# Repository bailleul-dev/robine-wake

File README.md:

# Robine Wake

Robine Wake is a privacy-first smart alarm clock for Raspberry Pi 3, Nerves,
and HiFiBerry, with a planned DIY bed-vibration channel for breathing, music
and progressive waking. The MVP runs fully on `host` with simulated
hardware, while preserving target adapters for the real device.

The product scope was updated on 2026-09-06: camera and bed-presence features are
removed. Their existing implementation still needs removal; the tactile extension
is specified but not implemented. See the
[bed-vibration specification](docs/specs/30/004-bed-vibration/spec.md) and the
[scope and migration status](docs/MVP_STATUS.md).

## Run on a development computer

Copy the public environment template once. The resulting `.env` is ignored by
Git and is loaded automatically by the Make targets and release scripts:

```sh
cp .env.dist .env
```

The host build does not require any private value. Leave optional entries empty
when they do not apply to your setup.

If a credential was committed before this setup existed, moving it to `.env`
does not remove it from Git history. Rotate that credential and either publish
from a fresh history or purge the old objects before making the repository
public.

```sh
mix deps.get
mix verify
mix run --no-halt
```

`mix verify` checks formatting, compiles with warnings treated as errors, runs
Credo in strict mode, audits Hex dependencies, and runs the complete host suite.
ExCoveralls enforces 67% production-code coverage and writes the browsable report
to `cover/excoveralls.html`; test-support modules are excluded from the metric.
The command also writes the scenario and requirements summary to
`cover/mvp-report.json`.

The individual quality checks are available while iterating:

```sh
mix credo --strict
mix coveralls
mix coveralls.html
```

Open <http://localhost:4110>. The local web interface has no login or password.
The HTTP port can be changed with `ROBINE_WEB_PORT`.

An MCP Streamable HTTP endpoint is available at
`http://localhost:4110/mcp`. It exposes device state and revision-safe alarm and
wake-session tools. Configure the client on the trusted local network and see
the [HTTP MCP specification](docs/specs/50/002-http-mcp/spec.md) for the complete
contract and security profile.

The host build also starts a Phoenix LiveView Hardware Lab at
<http://127.0.0.1:4111>. It emulates HiFiBerry availability and failures, network
loss, clock trust,
deterministic time advancement, alarms, snooze, and dismissal through the real
domain processes. Existing camera simulation controls are legacy functionality
scheduled for removal; tactile simulation is specified and remains to be added.
Change its port with `ROBINE_DEV_PORT`. The laboratory is loopback-only and its
Phoenix/LiveView code is excluded from Raspberry Pi compilation. See the
[host hardware emulator specification](docs/specs/80/002-host-hardware-emulator/spec.md).

### Demo mode

The same server can run as a public demo on a standard server, with the
hardware emulated: the product web app and a photoreal 3D bedroom (the sound
bar, its lights, the bedside remote, the sound) side by side at `/demo`. Every
action goes through the real server logic, routed to emulated drivers, with an
accelerated clock to watch a dawn in a few minutes.

```sh
ROBINE_DEMO=1 ROBINE_DEMO_ACCESS_CODE=change-me mix run --no-halt
open http://localhost:8080/demo
```

With Docker (set `ROBINE_DEMO_ACCESS_CODE` in `.env`):

```sh
docker compose up -d --build
```

The image uses the committed web build in `priv/web`; run `make expo-web`
first to refresh it. See the
[demo deployment section](docs/specs/80/002-host-hardware-emulator/spec.md#demo-deployment).

The public instance runs in the k3s cluster managed by `../silo01`, like the
other apps there. `make docker-build-and-push` builds the image for the
cluster, tagged with the current commit (uncommitted changes are refused), and
pushes it to the registry; `make robine-wake-demo-deploy ROBINE_WAKE_DEMO_VERSION=<tag>`
in `../silo01` rolls it out to <https://robine-wake-demo.bailleul.dev/demo>.
A demo release is a `demo-v*` tag of main (`make demo-release RELEASE=demo-v0.2.0`):
its CI (`.github/workflows/ci.yml`, on robine-actions' runners) runs the host
tests, builds and pushes the image tagged with it, then robine-actions rolls it
out; silo01 never builds.

The Raspberry Pi web interface is intentionally passwordless and intended only
for the trusted local network. Firmware updates and SSH remain authenticated.

## Experimental prototypes

The [`experimental/`](experimental/README.md) directory holds throwaway
evaluation prototypes that are **not part of the product**: they are not built
by `mix verify`, not shipped in the firmware, not deployed in the demo. The
current one is a Rust port of the alarm API used to evaluate a future
Buildroot-based system on custom hardware.

## Website and documentation

The marketing page and the technical documentation (generated from `docs/`) live
in [`website/`](website/README.md), an Astro / Starlight project:
`make site-dev`, `make site-build`.

## Mobile app

The iOS and Android application is the Expo / React Native project, written in
Gleam, in
[`mobile/`](mobile/README.md). `make expo-iphone` installs it on a local iPhone,
`make ios-beta` uploads it to TestFlight and `make play-store` to Google Play.

> The BLE control service is disabled on the Raspberry Pi firmware: the onboard
> controller now serves the [Bluetooth audio receiver](docs/specs/30/005-bluetooth-audio-receiver/spec.md).
> On the device, the app only reaches the clock over Wi-Fi.

The stable versioned command envelope, GATT UUIDs, paged response header, CRC32
validation, compatibility rules, and supported operations are documented in the
[Bluetooth v1 contract](docs/bluetooth/v1.md).

## LED strip

The light comes from a 60-LED WS2812B strip driven by the ESP32 co-processor,
which the Pi commands over UART (`light.program`). No bridge, cloud account or
network light is involved.

- **Dawn.** Each alarm can raise a dawn on the strip over its pre-wake ramp, so
  that full daylight arrives at the alarm time. Snooze turns the strip off and
  resuming starts it again; dismissal turns it off or leaves it lit, per alarm.
- **Evening breathing.** The `Soir` screen starts a guided breathing session at
  a cadence picked from named patterns (or typed in) and a duration: the strip
  breathes while the speaker plays the meditation ambience at the chosen volume. An alarm takes over the strip.
- **Reading light.** On the `Soir` screen, a warm amber at the bottom of the
  vertical strip to read by, orange then red towards the top, for up to 4
  hours, then an optional sunset of up to 2 hours.
- **Ambience.** A program can play a sound along, such as the storm and rain:
  it lowers to silence as the light fades and stops with it.
- **Manual programs.** The same screen starts a sunrise or a sunset of 1 minute
  to 4 hours, or turns the strip off. It also reads the strip back, pixel by
  pixel.

Strip failures are logged and never prevent the local audio alarm from running.

## Build for Raspberry Pi 3

```sh
make firmware
```

Without Wi-Fi values in `.env`, the firmware still builds and uses Ethernet
only. Set `ROBINE_WIFI_SSID` and `ROBINE_WIFI_PASSPHRASE` to provision Wi-Fi in
your local image.

Production updates are accepted only when signed by the Ed25519 key whose
public half is embedded in the firmware. The private half is intentionally
kept outside the repository. Build and verify a signed update with:

```sh
scripts/build_signed_firmware.sh
```

For a headless first boot, provide the WPA2 network only while building. The
credentials are embedded in the resulting device image but are never written
to the repository or printed by the build:

```sh
cp .env.dist .env
# Fill ROBINE_WIFI_* and ROBINE_FWUP_PRIVATE_KEY in .env, then:
scripts/build_signed_firmware.sh
```

After flashing and booting, open `http://robine-wake.local:4000/`. Raspberry Pi
3 models without dual-band Wi-Fi must use a 2.4 GHz network.

On this development machine the generated private key is stored with mode
`0600` under `~/.config/robine-wake/`; back it up securely before relying on it
for deployed devices. Updates are refused while a wake session is active, when
the clock is untrusted, or within 15 minutes of the next alarm. Nerves then
uses its inactive A/B slot and startup validation guard.

The HiFiBerry Amp2 is validated as `plughw:0` with the
`hifiberry-dacplus` Device Tree overlay. Target firmware also advertises
`Robine Wake Bedroom` as an AirPlay 2 receiver (`robine-airplayd`). An alarm always preempts
an active stream and the receiver returns after alarm playback ends. Each alarm
selects two sounds: a progressive wake track and a strong fallback track that
starts if the gentle ramp completes without dismissal. Curated MP3 assets and
their manifest live in `priv/sounds`; validated custom WAV files remain under
the persistent `/data/sounds` directory. The DIY tactile assembly and its firmware
integration remain validation items. See
[the specifications](docs/specs/README.md) and
[the MVP implementation status](docs/MVP_STATUS.md). The
[requirements matrix](docs/REQUIREMENTS_TRACEABILITY.md) records verified,
partial, deferred, and hardware-dependent requirements individually.

### Arrêt du réveil

L’arrêt depuis l’iPhone et le web est désactivé côté réveil : le bouton physique
reste disponible. Le réglage distant est verrouillé, y compris lorsqu’une ancienne
préférence autorisait l’arrêt depuis le smartphone. La fonctionnalité est conservée
et peut être réactivée dans le firmware avec `remote_dismiss_enabled: true` dans
`config/config.exs`.

## Build for Raspberry Pi Zero W

The `rpi0` target (ARMv6, one core, 512 MB) reuses the application and the
Pi 3 build options, with its own system in `nerves_system_rpi0` (upstream Nerves
Zero system plus BlueZ/A2DP, `speaker-test` and the HiFiBerry overlays) and
its own `config/rpi0-config.txt` / `config/rpi0-fwup.conf`. The Pi 3 files are
unchanged.

```sh
make firmware-rpi0                      # MIX_TARGET=rpi0 make firmware
make burn-sd MIX_TARGET=rpi0 DEVICE=/dev/diskN
```

The Zero has no Ethernet: the micro-USB *data* port is an Ethernet gadget
(`usb0`) for a first access, and `wlan0` takes the Wi-Fi values from `.env`.
The LoRa radio is disabled on this target (its SPI chip select is claimed by the
amplifier HAT). The ESP32 guide light uses the same UART as the Pi 3 (GPIO 14/15):
the amplifier overlay is `merus-amp-uart` in `config/rpi0-config.txt`
(InnoMaker MA12070P HAT), the stock `merus-amp` overlay without its enable/mute
lines. See the wiring guide before connecting the ESP32. The first build
compiles the whole Buildroot system, which takes a while; it is not
cross-built from the Pi 3 artifacts.

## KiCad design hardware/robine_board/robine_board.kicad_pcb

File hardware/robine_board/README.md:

# Robine Wake — All-In-One Mainboard v1.1 (`robine_board`)

> **Statut : schéma v1.1 terminé, PCB placé mais non routé.** Les exports de
> fabrication (`exports/gerbers/`) reflètent cet état et **ne sont pas
> commandables**. La revue [`DESIGN_REVIEW.md`](DESIGN_REVIEW.md) porte sur la
> v1.0 ; une partie de ses points a été traitée par la v1.1.

Carte électronique principale tout-en-un du réveil / barre de son **Robine
Wake**, conçue sous **KiCad 9** via le serveur MCP `kicad`. Carte 2 couches,
120 × 90 mm, 145 composants.

Pour prototyper sans cette carte, voir le banc de dev sur breadboard :
[`../dev_bench/banc-de-dev.pdf`](../dev_bench/banc-de-dev.pdf).

---

## 1. Vue d'ensemble des sous-systèmes

| Sous-système | Référence(s) | Composant choisi | Caractéristiques clés |
| :--- | :--- | :--- | :--- |
| **MCU principal** | `U1`, `SW1`, `SW2`, `J3`, `U11`, `J4` | `ESP32-S3-WROOM-1-N16R8` | Dual-core LX7 240 MHz, 16 Mo flash, 8 Mo PSRAM octale, Wi-Fi + BLE 5. AirPlay 2, maître I²S, SPI et I²C. USB-C natif (`J3`, protection ESD `U11` `USBLC6-2SC6`, CC 5,1 kΩ `R22`/`R23`), console UART0 sur `J4` |
| **Co-processeur Bluetooth audio + aube** | `U2`, `J9`, `R25`, `R26`, `C29` | `ESP32-WROOM-32E` | Bluetooth Classic BR/EDR (A2DP sink, AVRCP), absent du S3. Esclave I²S de `U1` (`I2S_BCLK`, `I2S_LRCLK`), renvoie le flux A2DP sur `I2S_BT_DOUT`. Relié à `U1` par son UART0 ; `U1` pilote `BT_EN` et `BT_IO0` et peut le reflasher via le bootloader ROM. `J9` (`BT_PROG`) en parallèle pour la récupération manuelle. Génère aussi les 10 PWM de l'aube |
| **Entrée secteur 24 V** | `J1`, `D1`, `C1` | Bornier 2 points + `SS54` | Entrée `+24V_MAINS`, OR-ing vers `PVDD_24V` par `D1` |
| **UPS batterie 4S LiFePO4** | `J2`, `U3`, `Q1`, `L7`, `R15`, `R1`/`R2` | `BQ24610` + `CSD87350Q5D` | Chargeur buck synchrone depuis `+24V_MAINS`, shunt 10 mΩ, tension de fin de charge fixée par `R1`/`R2` (110 k / 20 k ≈ 13,6 V). `MAINS_OK` (/PG) et `CHG_STAT` (STAT1) vers `U1` |
| **Boost batterie → PVDD** | `U10`, `L8`, `D2`, `R16`/`R17`, `D3` | `TPS55340` | Remonte `+VBAT` vers ≈ 23,4 V sur `PVDD_24V` (OR-ing `D2`), activé par `BOOST_EN`. `D3` relie directement `+VBAT` à `PVDD_24V` en dernier recours |
| **Rails logiques** | `U4`, `L1`, `D5`, `U5`, `L6`, `D6` | `TPS54531` + `TPS54331` | Buck `PVDD_24V` → `+5V` (5 A, `R18`/`R19`), puis buck `+5V` → `+3V3` (3 A, `R20`/`R21`) |
| **Ampli stéréo** | `U6`, `L2..L5`, `C11..C14`, `C9`, `J5`, `R10` | `TAS5825M` (HTSSOP-32) | Classe D sur `PVDD_24V`, entrée I²S (`I2S_DOUT`), contrôle I²C, adresse fixée par `R10` (4,7 kΩ sur `ADR`). Filtre LC BTL vers `J5` (4 points) |
| **LoRa 868 MHz** | `U7`, `J6` | `Ai-Thinker Ra-01H` (SX1276) + SMA | Sur le SPI partagé, `LORA_CS`, `LORA_RST`, `LORA_DIO0`. Lien avec le bouton déporté `ACC-003` |
| **Stockage** | `U8` | `W25N01GVZEIG` | NAND SPI 1 Gbit sur le SPI partagé (`NAND_CS`) |
| **Horloge temps réel** | `U9`, `BT1` | `DS3231MZ` + CR1220 | I²C partagé avec l'ampli, alarme `RTC_INT_N` vers `U1`, sauvegarde par pile |
| **Lampes d'aube (10 canaux)** | `U12..U21`, `L11..L20`, `D11..D20`, `R31..R40`, `J7`, `J8`, `J10` | 10 × `PT4115` | Drivers LED à courant constant (shunt 0,2 Ω ≈ 0,5 A) alimentés par `+24V_MAINS`, gradation par `PWM_CH1..10` depuis `U2`. Lampe 1 (`J7`) et lampe 2 (`J8`) : blanc chaud, blanc froid, ambre. Halo (`J10`) : R, G, B, ambre |
| **LED de statut** | `D4`, `R9` | `SK6812` | Une LED adressable sur `+5V`, données `STATUS_LED_3V3` via 330 Ω |

---

## 2. Mapping GPIO de `U1` (`ESP32-S3-WROOM-1-N16R8`)

Généré à partir du netlist du schéma v1.1. Broches non listées : non connectées
(IO3, IO45, IO46 ; IO35..IO37 sont réservées à la PSRAM octale).

| Fonction | Net | Broche `U1` | GPIO | Cible(s) |
| :--- | :--- | :---: | :--- | :--- |
| Reset | `MCU_EN` | 3 | `EN` | `R24` 10 kΩ, `C7` 1 µF, bouton `SW1` |
| Boot | `MCU_BOOT` | 27 | `GPIO0` | `R12` 10 kΩ, bouton `SW2` |
| Présence secteur | `MAINS_OK` | 4 | `GPIO4` | `U3` /PG, pull-up `R8` |
| Commande boost | `BOOST_EN` | 5 | `GPIO5` | `U10` EN, pull-down `R13` |
| ADC batterie | `ADC_VBAT_SENSE` | 39 | `GPIO1` (ADC1_CH0) | Pont `R3` 100 kΩ / `R4` 15 kΩ sur `+VBAT` |
| État charge | `CHG_STAT` | 38 | `GPIO2` | `U3` STAT1, pull-up `R5` |
| I²S horloge bit | `I2S_BCLK` | 6 | `GPIO6` | `U6` SCLK + `U2` IO26 |
| I²S horloge mot | `I2S_LRCLK` | 7 | `GPIO7` | `U6` LRCLK + `U2` IO25 |
| I²S vers ampli | `I2S_DOUT` | 12 | `GPIO8` | `U6` SDIN |
| I²S depuis BT | `I2S_BT_DOUT` | 33 | `GPIO40` | `U2` IO22 (flux A2DP) |
| I²C données | `I2C_SDA` | 10 | `GPIO17` | `U6`, `U9`, pull-up `R6` 4,7 kΩ |
| I²C horloge | `I2C_SCL` | 11 | `GPIO18` | `U6`, `U9`, pull-up `R7` 4,7 kΩ |
| Ampli marche | `AMP_PDN` | 23 | `GPIO21` | `U6` /PDN |
| Ampli défaut | `AMP_FAULT` | 31 | `GPIO38` | `U6` /FAULT, pull-up `R11` |
| SPI horloge | `SPI_SCK` | 20 | `GPIO12` | `U7`, `U8` |
| SPI MOSI | `SPI_MOSI` | 19 | `GPIO11` | `U7`, `U8` |
| SPI MISO | `SPI_MISO` | 21 | `GPIO13` | `U7`, `U8` |
| LoRa sélection | `LORA_CS` | 18 | `GPIO10` | `U7` NSS, pull-up `R27` |
| LoRa reset | `LORA_RST` | 22 | `GPIO14` | `U7` RESET |
| LoRa interruption | `LORA_DIO0` | 32 | `GPIO39` | `U7` DIO0 |
| NAND sélection | `NAND_CS` | 17 | `GPIO9` | `U8` /CS, pull-up `R28` |
| RTC alarme | `RTC_INT_N` | 34 | `GPIO41` | `U9` /INT, pull-up `R14` |
| LED statut | `STATUS_LED_3V3` | 35 | `GPIO42` | `R9` 330 Ω → `D4` DIN |
| Liaison BT (TX de `U1`) | `BT_RXD0` | 8 | `GPIO15` | `U2` RXD0, `J9` broche 3 |
| Liaison BT (RX de `U1`) | `BT_TXD0` | 9 | `GPIO16` | `U2` TXD0, `J9` broche 2 |
| Reset de `U2` | `BT_EN` | 24 | `GPIO47` | `U2` EN, `R25`, `C29`, `J9` broche 5 — en open-drain |
| Boot de `U2` | `BT_IO0` | 25 | `GPIO48` | `U2` IO0, `R26`, `J9` broche 4 — en open-drain |
| USB natif | `USB_DN`, `USB_DP` | 13, 14 | `GPIO19`, `GPIO20` | `U11` → `J3` |
| Console | `UART0_TX`, `UART0_RX` | 37, 36 | `GPIO43`, `GPIO44` | `J4` |

Quand un adaptateur est branché sur `J9`, laisser `GPIO15` en entrée : il est
en parallèle de la sortie TX de l'adaptateur.

## 3. Mapping GPIO de `U2` (`ESP32-WROOM-32E`)

| Fonction | Net | GPIO | Cible |
| :--- | :--- | :--- | :--- |
| Liaison avec `U1` | `BT_RXD0`, `BT_TXD0` | `GPIO3`, `GPIO1` (UART0) | `U1` GPIO15, GPIO16 |
| Reset, boot | `BT_EN`, `BT_IO0` | `EN`, `GPIO0` | `U1` GPIO47, GPIO48 |
| I²S esclave | `I2S_BCLK`, `I2S_LRCLK` | `GPIO26`, `GPIO25` | horloges générées par `U1` |
| Sortie A2DP | `I2S_BT_DOUT` | `GPIO22` | `U1` GPIO40 |
| Lampe 1 blanc chaud, froid, ambre | `PWM_CH1..3` | `GPIO4`, `GPIO13`, `GPIO14` | `U12..U14` DIM |
| Lampe 2 blanc chaud, froid, ambre | `PWM_CH4..6` | `GPIO18`, `GPIO19`, `GPIO21` | `U15..U17` DIM |
| Halo R, G, B, ambre | `PWM_CH7..10` | `GPIO23`, `GPIO27`, `GPIO32`, `GPIO33` | `U18..U21` DIM |

---

## 4. Vérifications

- **ERC** : 0 violation. **DRC** : 0 violation, parité schéma ↔ PCB sans
  écart ; 402 connexions restent à router.
- ERC et DRC ne contrôlent que la cohérence des symboles et empreintes tels
  que dessinés, pas leur conformité aux composants réels.

### Points ouverts

- **Routage** du PCB à faire, puis plans de masse et vias thermiques
  (`U6` PowerPAD, buck, boost).
- **Placement** : sur la vue 2D, des borniers et la zone d'antenne de `U1`
  débordent du contour de la carte.
- **Aube sur batterie** : les `PT4115` sont alimentés par `+24V_MAINS`, donc
  les lampes s'éteignent en cas de coupure secteur. À confirmer si c'est
  voulu.
- **LED de statut** : la `SK6812` est en 5 V et reçoit des données en 3,3 V
  sans level shifter ; le seuil haut (0,7 × VDD = 3,5 V) n'est pas garanti.

---

## 5. Fichiers

- **Sources KiCad**
  - [`robine_board.kicad_pro`](robine_board.kicad_pro) — projet KiCad 9
  - [`robine_board.kicad_sch`](robine_board.kicad_sch) — schéma
  - [`robine_board.kicad_pcb`](robine_board.kicad_pcb) — PCB 120 × 90 mm, placé, non routé
  - [`Robine_Custom.kicad_sym`](Robine_Custom.kicad_sym) — symboles dédiés
  - [`3dmodels/`](3dmodels) — modèles 3D des composants
- **Exports** (`exports/`, régénérés avec `kicad-cli` 9.0.8)
  - [`robine_board_schematic.pdf`](exports/robine_board_schematic.pdf), [`robine_board_schematic.png`](exports/robine_board_schematic.png) — schéma
  - [`robine_board_pcb.pdf`](exports/robine_board_pcb.pdf), [`robine_board_pcb.svg`](exports/robine_board_pcb.svg), [`robine_board_pcb_2d.png`](exports/robine_board_pcb_2d.png) — vue 2D (F.Cu, B.Cu, F.Silkscreen, Edge.Cuts)
  - [`robine_board_3d_iso.png`](exports/robine_board_3d_iso.png), [`robine_board_3d_top.png`](exports/robine_board_3d_top.png), [`robine_board_3d_bottom.png`](exports/robine_board_3d_bottom.png) — rendus 3D
  - [`robine_board.step`](exports/robine_board.step) — modèle 3D STEP
  - [`robine_board_bom.csv`](exports/robine_board_bom.csv) — nomenclature (145 composants, 68 lignes groupées)
  - [`robine_board_positions.csv`](exports/robine_board_positions.csv) — pick-and-place
  - [`drc_report.json`](exports/drc_report.json) — rapport DRC avec parité schéma
  - [`gerbers/`](exports/gerbers) — Gerber (cuivre, masque, pâte, sérigraphie, contour) et perçage Excellon, **non commandables tant que le PCB n'est pas routé**

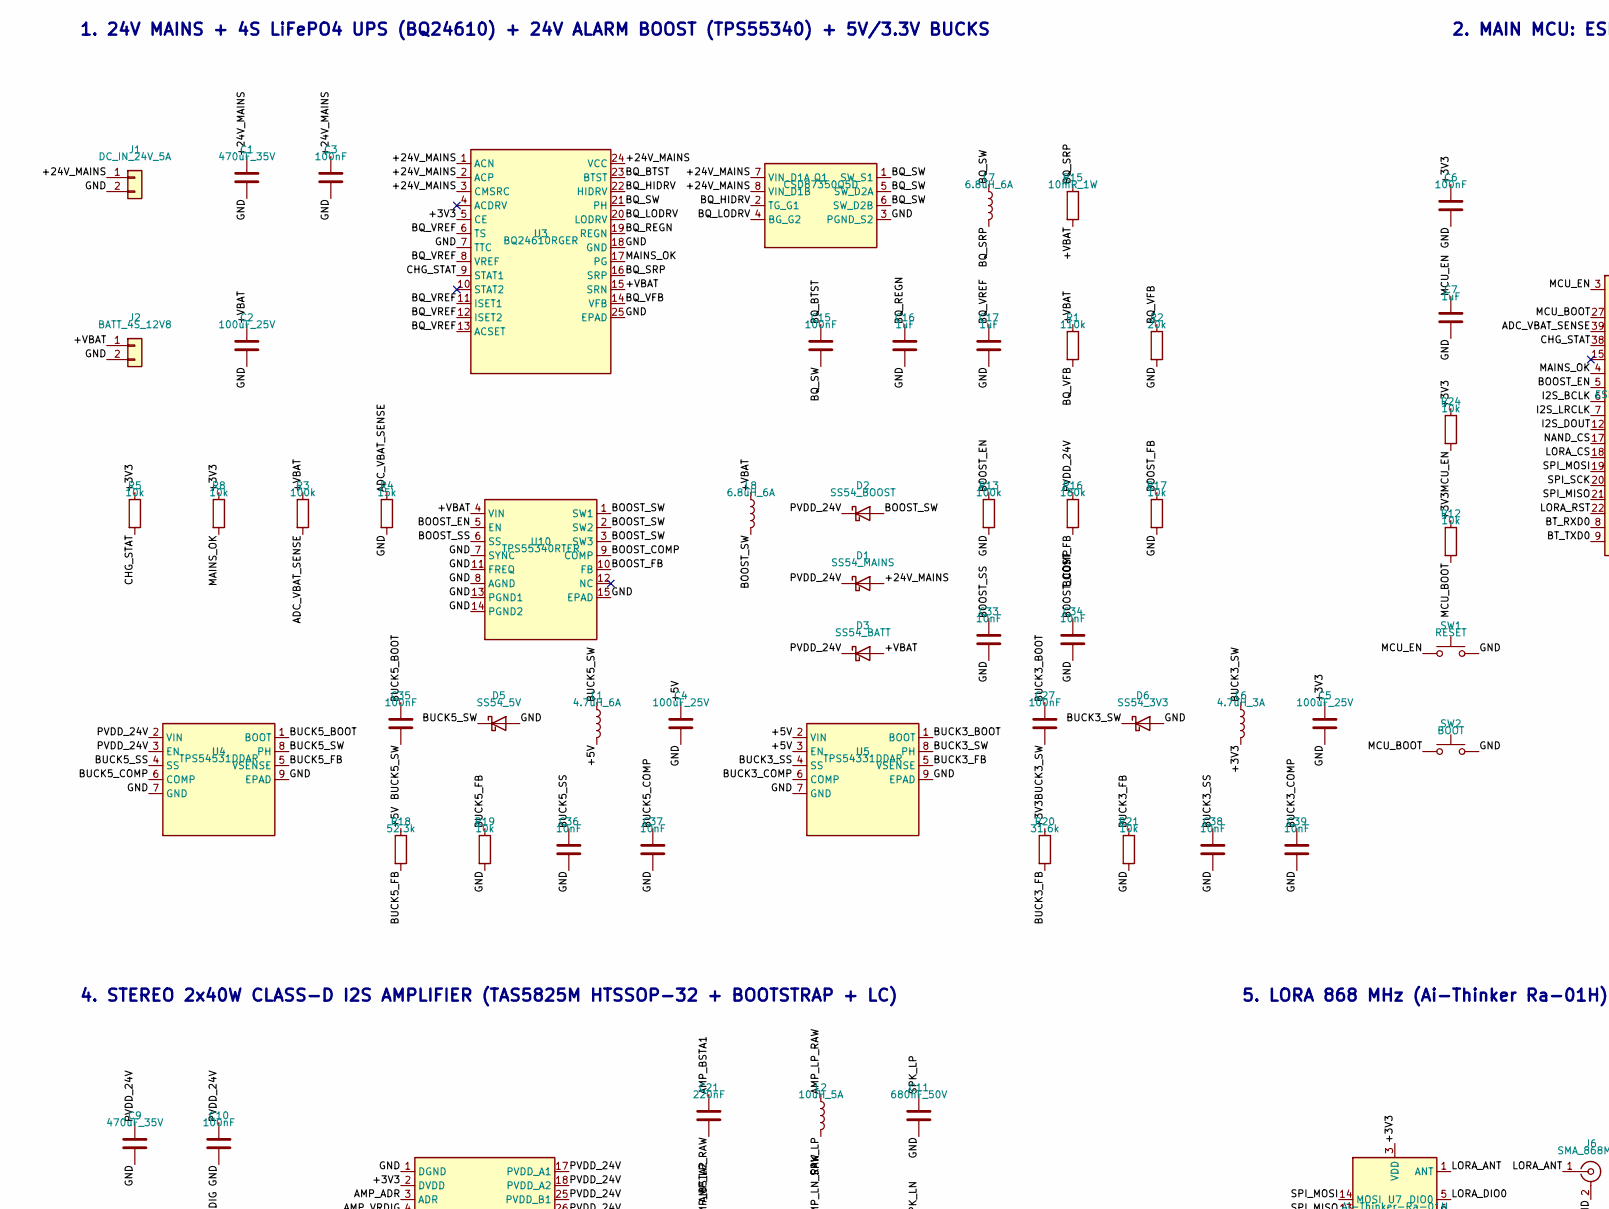
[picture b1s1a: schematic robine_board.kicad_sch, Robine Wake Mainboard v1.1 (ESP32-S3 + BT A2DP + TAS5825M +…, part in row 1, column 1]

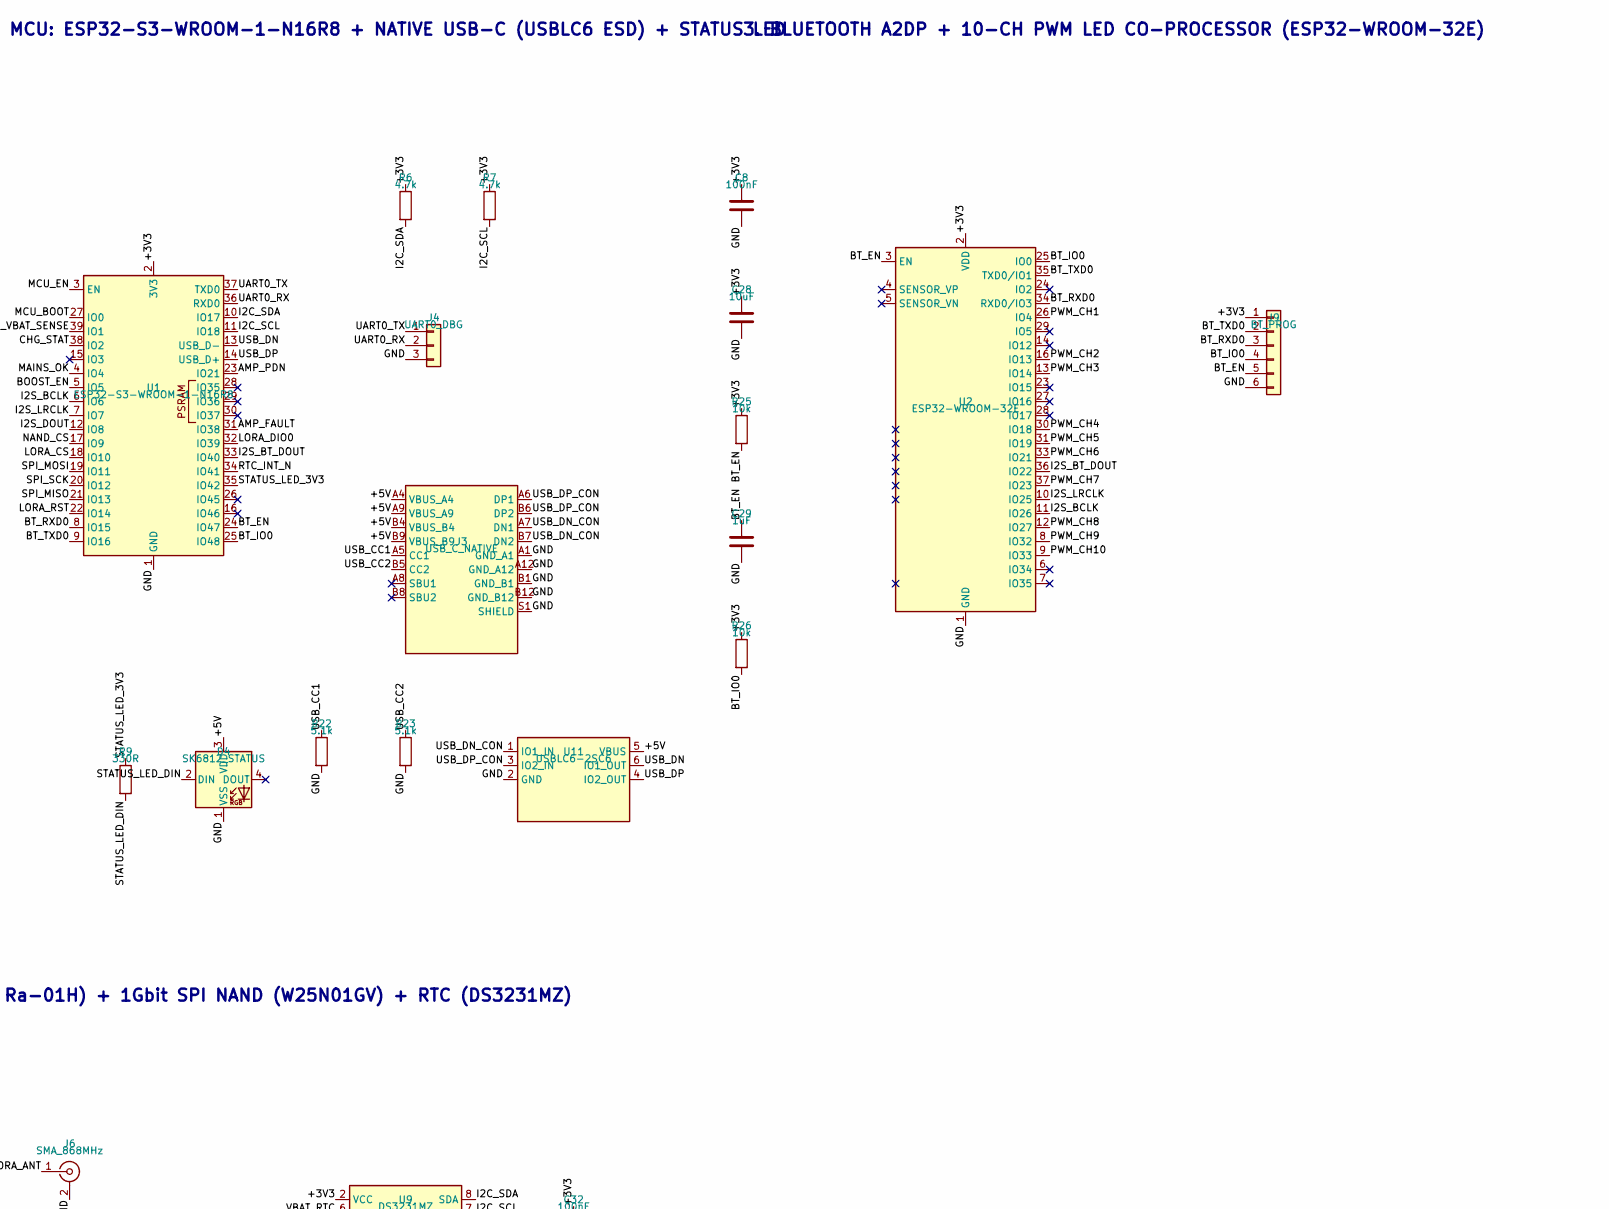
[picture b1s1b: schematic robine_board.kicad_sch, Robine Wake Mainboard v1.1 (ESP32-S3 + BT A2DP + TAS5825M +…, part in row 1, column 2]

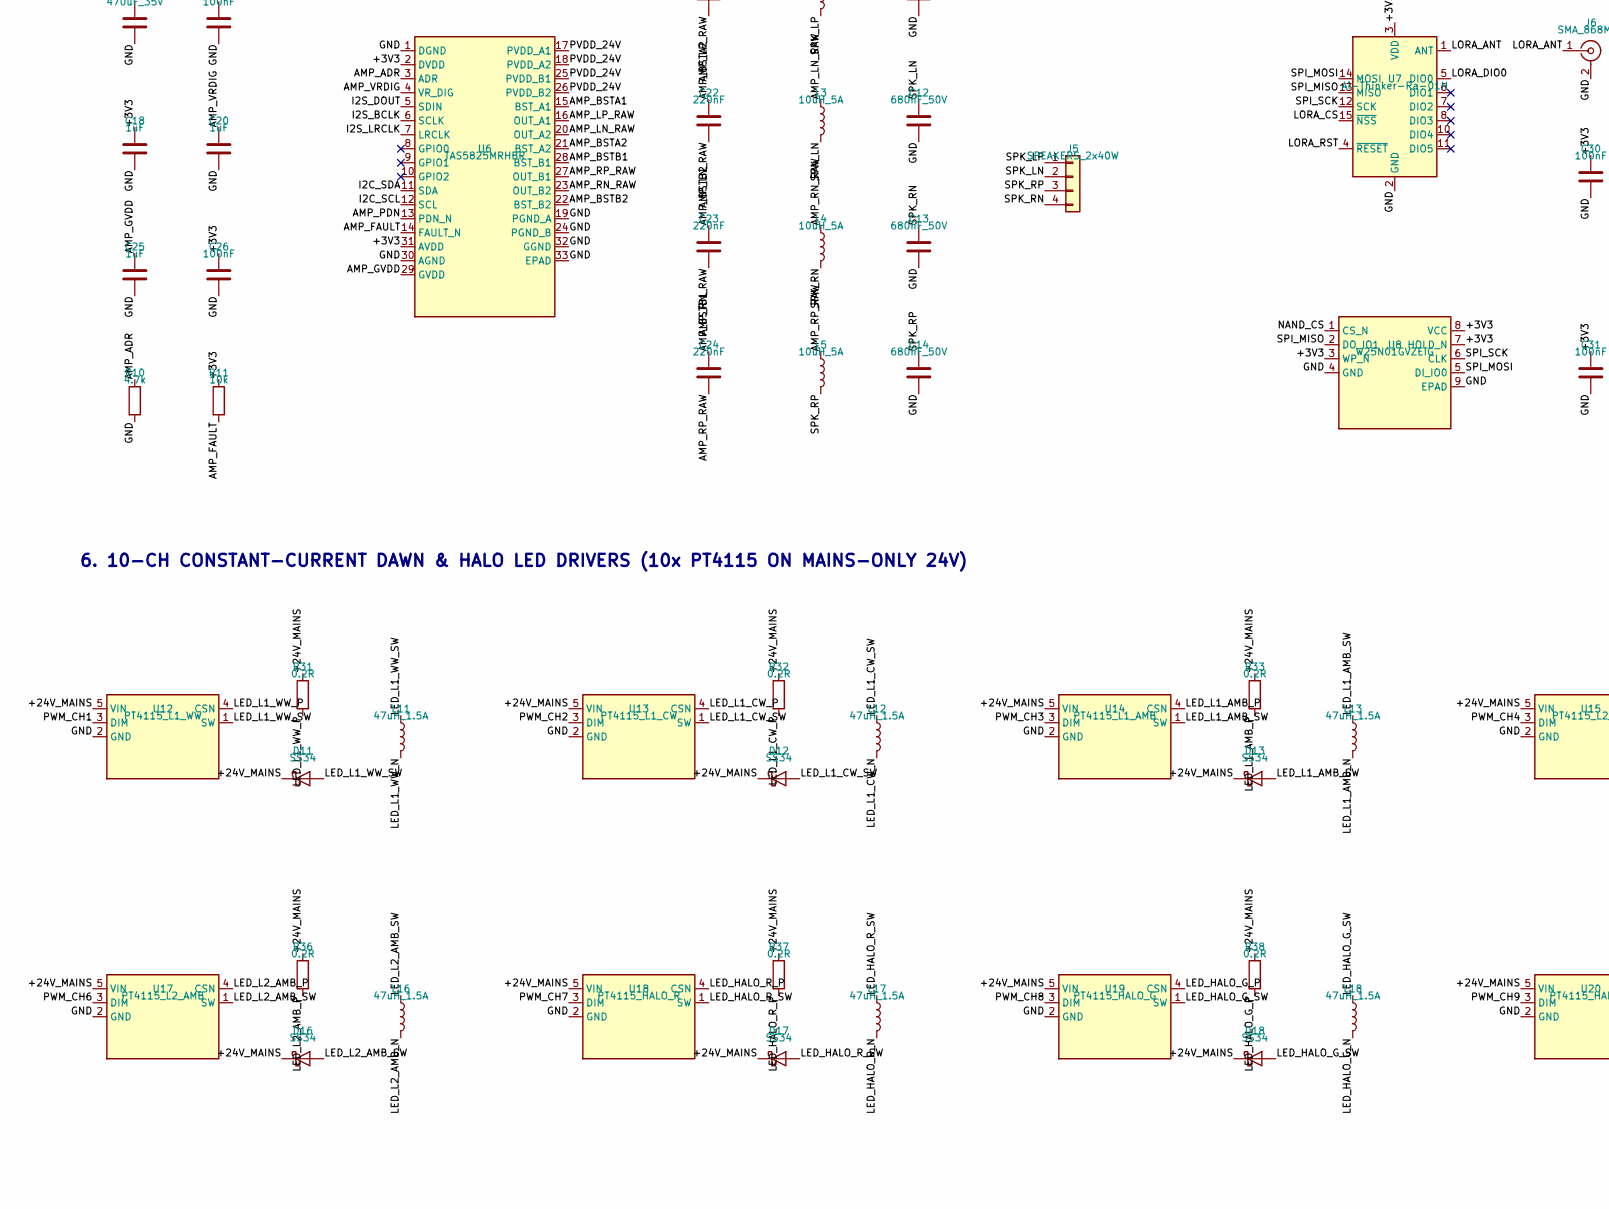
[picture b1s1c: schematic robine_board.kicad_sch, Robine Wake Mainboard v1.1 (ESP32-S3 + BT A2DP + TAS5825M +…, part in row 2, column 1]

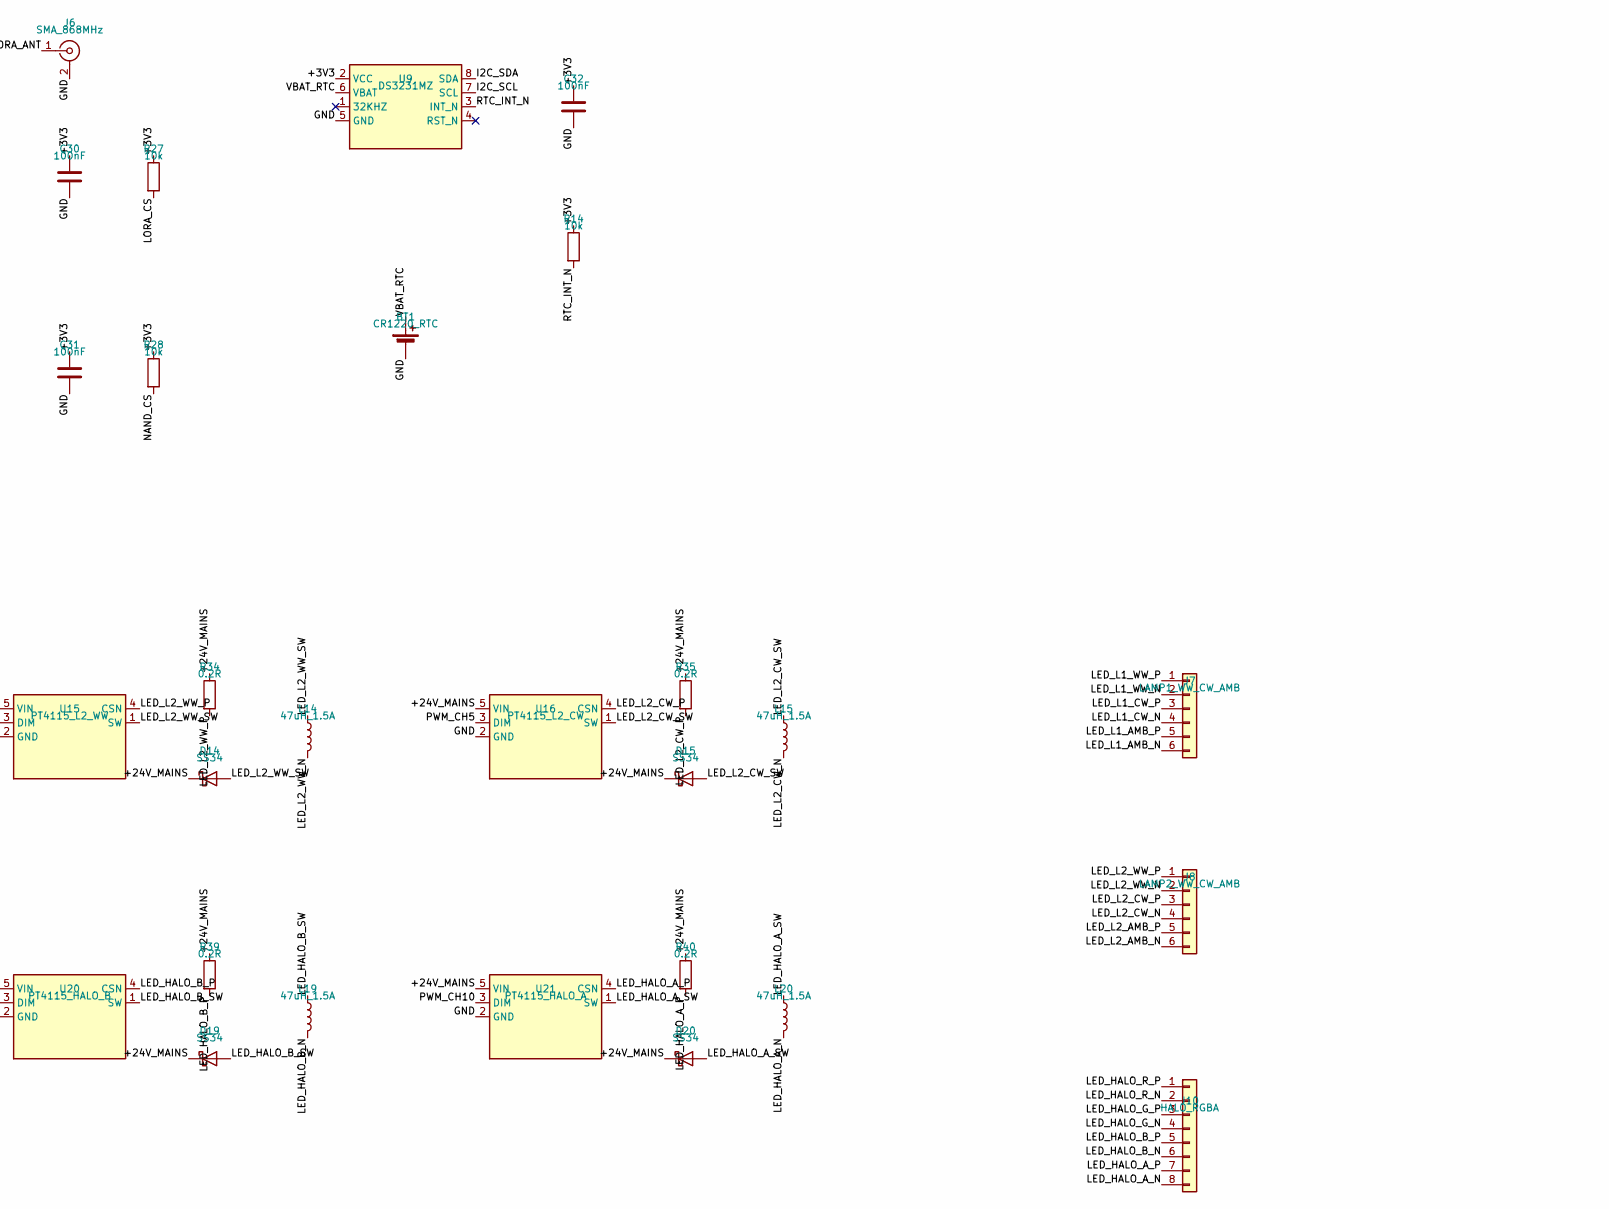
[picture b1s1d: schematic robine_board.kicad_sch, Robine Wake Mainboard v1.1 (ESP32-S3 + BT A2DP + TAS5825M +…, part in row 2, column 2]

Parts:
BT1: CR1220_RTC; Battery_Panasonic_CR1220-VCN_Vertical_CircularHoles
C1, C9: 470uF_35V; CP_Elec_10x10
C2, C4, C5: 100uF_25V; CP_Elec_6.3x7.7
C3, C6, C8, C10, C15, C26, C27, C30, C31, C32, C35: 100nF; C_0805_2012Metric
C7, C16, C17, C18, C20, C25, C29: 1uF; C_0805_2012Metric
C11, C12, C13, C14: 680nF_50V; C_0805_2012Metric
C21, C22, C23, C24: 220nF; C_0805_2012Metric
C28: 10uF; C_0805_2012Metric
C33, C34, C36, C37, C38, C39: 10nF; C_0805_2012Metric
D1: SS54_MAINS; D_SMA
D2: SS54_BOOST; D_SMA
D3: SS54_BATT; D_SMA
D4: SK6812_STATUS; LED_SK6812_PLCC4_5.0x5.0mm_P3.2mm
D5: SS54_5V; D_SMA
D6: SS54_3V3; D_SMA
D11, D12, D13, D14, D15, D16, D17, D18, D19, D20: SS34; D_SMA
J1: DC_IN_24V_5A; TerminalBlock_Phoenix_MKDS-1,5-2-5.08_1x02_P5.08mm_Horizont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
J2: BATT_4S_12V8; TerminalBlock_Phoenix_MKDS-1,5-2-5.08_1x02_P5.08mm_Horizont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
J3: USB_C_NATIVE; USB_C_Receptacle_GCT_USB4085
J4: UART0_DBG; PinHeader_1x03_P2.54mm_Vertical
J5: SPEAKERS_2x40W; TerminalBlock_Phoenix_MKDS-1,5-4-5.08_1x04_P5.08mm_Horizont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
J6: SMA_868MHz; SMA_Amphenol_132134_Vertical
J7: LAMP1_WW_CW_AMB; TerminalBlock_Phoenix_MKDS-1,5-6-5.08_1x06_P5.08mm_Horizont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
J8: LAMP2_WW_CW_AMB; TerminalBlock_Phoenix_MKDS-1,5-6-5.08_1x06_P5.08mm_Horizont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
J9: BT_PROG; PinHeader_1x06_P2.54mm_Vertical
J10: HALO_RGBA; TerminalBlock_Phoenix_MKDS-1,5-8-5.08_1x08_P5.08mm_Horizont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
L1: 4.7uH_6A; L_7.3x7.3_H4.5
L2, L3, L4, L5: 10uH_5A; L_7.3x7.3_H4.5
L6: 4.7uH_3A; L_6.3x6.3_H3
L7, L8: 6.8uH_6A; L_7.3x7.3_H4.5
L11, L12, L13, L14, L15, L16, L17, L18, L19, L20: 47uH_1.5A; L_6.3x6.3_H3
Q1: CSD87350Q5D; SOIC-8_3.9x4.9mm_P1.27mm
R1: 110k; R_0805_2012Metric
R2: 20k; R_0805_2012Metric
R3, R13: 100k; R_0805_2012Metric
R4: 15k; R_0805_2012Metric
R5, R8, R11, R12, R14, R17, R19, R21, R24, R25, R26, R27, R28: 10k; R_0805_2012Metric
R6, R7, R10: 4.7k; R_0805_2012Metric
R9: 330R; R_0805_2012Metric
R15: 10mR_1W; R_1206_3216Metric
R16: 180k; R_0805_2012Metric
R18: 52.3k; R_0805_2012Metric
R20: 31.6k; R_0805_2012Metric
R22, R23: 5.1k; R_0805_2012Metric
R31, R32, R33, R34, R35, R36, R37, R38, R39, R40: 0.2R; R_0805_2012Metric
SW1: RESET; SW_SPST_PTS645Sx43SMTR92
SW2: BOOT; SW_SPST_PTS645Sx43SMTR92
U1: ESP32-S3-WROOM-1-N16R8; ESP32-S3-WROOM-1
U2: ESP32-WROOM-32E
U3: BQ24610RGER; HVQFN-24-1EP_4x4mm_P0.5mm_EP2.5x2.5mm
U4: TPS54531DDAR; SOIC-8-1EP_3.9x4.9mm_P1.27mm_EP2.29x3mm
U5: TPS54331DDAR; SOIC-8-1EP_3.9x4.9mm_P1.27mm_EP2.29x3mm
U6: TAS5825MRHBR; HTSSOP-32-1EP_6.1x11mm_P0.65mm_EP5.2x11mm_Mask4.11x4.36mm
U7: Ai-Thinker-Ra-01H; Ai-Thinker-Ra-01-LoRa
U8: W25N01GVZEIG; WSON-8-1EP_8x6mm_P1.27mm_EP3.4x4.3mm
U9: DS3231MZ; SOIC-8_3.9x4.9mm_P1.27mm
U10: TPS55340RTER; Texas_HTSSOP-14-1EP_4.4x5mm_P0.65mm_EP3.4x5mm_Mask3.155x3.2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
U11: USBLC6-2SC6; SOT-23-6
U12: PT4115_L1_WW; SOT-89-5
U13: PT4115_L1_CW; SOT-89-5
U14: PT4115_L1_AMB; SOT-89-5
U15: PT4115_L2_WW; SOT-89-5
U16: PT4115_L2_CW; SOT-89-5
U17: PT4115_L2_AMB; SOT-89-5
U18: PT4115_HALO_R; SOT-89-5
U19: PT4115_HALO_G; SOT-89-5
U20: PT4115_HALO_B; SOT-89-5
U21: PT4115_HALO_A; SOT-89-5

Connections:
/+3V3: C5.1, C6.1, C8.1, C18.1, C26.1, C28.1, C30.1, C31.1, C32.1, J9.1, L6.2, R5.1, R6.1, R7.1, R8.1, R11.1, R12.1, R14.1, R20.1, R24.1, R25.1, R26.1, R27.1, R28.1, U1.2 (3V3), U2.2 (VDD), U3.5 (CE), U6.2 (DVDD), U6.31 (AVDD), U7.3 (VDD), U8.3 (WP_N), U8.7 (HOLD_N), U8.8 (VCC), U9.2 (VCC)
/+5V: C4.1, D4.3 (VDD), J3.A4 (VBUS_A4), J3.A9 (VBUS_A9), J3.B4 (VBUS_B4), J3.B9 (VBUS_B9), L1.2, R18.1, U5.2 (VIN), U5.3 (EN), U11.5 (VBUS)
/+24V_MAINS: C1.1, C3.1, D1.2 (A), D11.1 (K), D12.1 (K), D13.1 (K), D14.1 (K), D15.1 (K), D16.1 (K), D17.1 (K), D18.1 (K), D19.1 (K), D20.1 (K), J1.1, Q1.7 (VIN_D1A), Q1.8 (VIN_D1B), R31.1, R32.1, R33.1, R34.1, R35.1, R36.1, R37.1, R38.1, R39.1, R40.1, U3.1 (ACN), U3.2 (ACP), U3.3 (CMSRC), U3.24 (VCC), U12.5 (VIN), U13.5 (VIN), U14.5 (VIN), U15.5 (VIN), U16.5 (VIN), U17.5 (VIN), U18.5 (VIN), U19.5 (VIN), U20.5 (VIN), U21.5 (VIN)
/+VBAT: C2.1, D3.2 (A), J2.1, L8.1, R1.1, R3.1, R15.2, U3.15 (SRN), U10.4 (VIN)
/ADC_VBAT_SENSE: R3.2, R4.1, U1.39 (IO1)
/AMP_ADR: R10.1, U6.3 (ADR)
/AMP_BSTA1: C21.1, U6.15 (BST_A1)
/AMP_BSTA2: C22.1, U6.21 (BST_A2)
/AMP_BSTB1: C24.1, U6.28 (BST_B1)
/AMP_BSTB2: C23.1, U6.22 (BST_B2)
/AMP_FAULT: R11.2, U1.31 (IO38), U6.14 (FAULT_N)
/AMP_GVDD: C25.1, U6.29 (GVDD)
/AMP_LN_RAW: C22.2, L3.1, U6.20 (OUT_A2)
/AMP_LP_RAW: C21.2, L2.1, U6.16 (OUT_A1)
/AMP_PDN: U1.23 (IO21), U6.13 (PDN_N)
/AMP_RN_RAW: C23.2, L4.1, U6.23 (OUT_B2)
/AMP_RP_RAW: C24.2, L5.1, U6.27 (OUT_B1)
/AMP_VRDIG: C20.1, U6.4 (VR_DIG)
/BOOST_COMP: C34.1, U10.9 (COMP)
/BOOST_EN: R13.1, U1.5 (IO5), U10.5 (EN)
/BOOST_FB: R16.2, R17.1, U10.10 (FB)
/BOOST_SS: C33.1, U10.6 (SS)
/BOOST_SW: D2.2 (A), L8.2, U10.1 (SW1), U10.2 (SW2), U10.3 (SW3)
/BQ_BTST: C15.1, U3.23 (BTST)
/BQ_HIDRV: Q1.2 (TG_G1), U3.22 (HIDRV)
/BQ_LODRV: Q1.4 (BG_G2), U3.20 (LODRV)
/BQ_REGN: C16.1, U3.19 (REGN)
/BQ_SRP: L7.2, R15.1, U3.16 (SRP)
/BQ_SW: C15.2, L7.1, Q1.1 (SW_S1), Q1.5 (SW_D2A), Q1.6 (SW_D2B), U3.21 (PH)
/BQ_VFB: R1.2, R2.1, U3.14 (VFB)
/BQ_VREF: C17.1, U3.6 (TS), U3.8 (VREF), U3.11 (ISET1), U3.12 (ISET2), U3.13 (ACSET)
/BT_EN: C29.1, J9.5, R25.2, U1.24 (IO47), U2.3 (EN)
/BT_IO0: J9.4, R26.2, U1.25 (IO48), U2.25 (IO0)
/BT_RXD0: J9.3, U1.8 (IO15), U2.34 (RXD0/IO3)
/BT_TXD0: J9.2, U1.9 (IO16), U2.35 (TXD0/IO1)
/BUCK3_BOOT: C27.1, U5.1 (BOOT)
/BUCK3_COMP: C39.1, U5.6 (COMP)
/BUCK3_FB: R20.2, R21.1, U5.5 (VSENSE)
/BUCK3_SS: C38.1, U5.4 (SS)
/BUCK3_SW: C27.2, D6.1 (K), L6.1, U5.8 (PH)
/BUCK5_BOOT: C35.1, U4.1 (BOOT)
/BUCK5_COMP: C37.1, U4.6 (COMP)
/BUCK5_FB: R18.2, R19.1, U4.5 (VSENSE)
/BUCK5_SS: C36.1, U4.4 (SS)
/BUCK5_SW: C35.2, D5.1 (K), L1.1, U4.8 (PH)
/CHG_STAT: R5.2, U1.38 (IO2), U3.9 (STAT1)
/GND: BT1.2 (-), C1.2, C2.2, C3.2, C4.2, C5.2, C6.2, C7.2, C8.2, C9.2, C10.2, C11.2, C12.2, C13.2, C14.2, C16.2, C17.2, C18.2, C20.2, C25.2, C26.2, C28.2, C29.2, C30.2, C31.2, C32.2, C33.2, C34.2, C36.2, C37.2, C38.2, C39.2, D4.1 (VSS), D5.2 (A), D6.2 (A), J1.2, J2.2, J3.A1 (GND_A1), J3.A12 (GND_A12), J3.B1 (GND_B1), J3.B12 (GND_B12), J3.S1 (SHIELD), J4.3, J6.2 (Ext), J9.6, Q1.3 (PGND_S2), R2.2, R4.2, R10.2, R13.2, R17.2, R19.2, R21.2, R22.2, R23.2, SW1.2, SW2.2, U1.1 (GND), U1.40 (GND), U1.41 (GND), U2.1 (GND), U2.15 (GND), U2.38 (GND), U2.39 (GND), U3.7 (TTC), U3.18 (GND), U3.25 (EPAD), U4.7 (GND), U4.9 (EPAD), U5.7 (GND), U5.9 (EPAD), U6.1 (DGND), U6.19 (PGND_A), U6.24 (PGND_B), U6.30 (AGND), U6.32 (GGND), U6.33 (EPAD), U7.2 (GND), U7.9 (GND), U7.16 (GND), U8.4 (GND), U8.9 (EPAD), U9.5 (GND), U10.7 (SYNC), U10.8 (AGND), U10.11 (FREQ), U10.13 (PGND1), U10.14 (PGND2), U10.15 (EPAD), U11.2 (GND), U12.2 (GND), U13.2 (GND), U14.2 (GND), U15.2 (GND), U16.2 (GND), U17.2 (GND), U18.2 (GND), U19.2 (GND), U20.2 (GND), U21.2 (GND)
/I2C_SCL: R7.2, U1.11 (IO18), U6.12 (SCL), U9.7 (SCL)
/I2C_SDA: R6.2, U1.10 (IO17), U6.11 (SDA), U9.8 (SDA)
/I2S_BCLK: U1.6 (IO6), U2.11 (IO26), U6.6 (SCLK)
/I2S_BT_DOUT: U1.33 (IO40), U2.36 (IO22)
/I2S_DOUT: U1.12 (IO8), U6.5 (SDIN)
/I2S_LRCLK: U1.7 (IO7), U2.10 (IO25), U6.7 (LRCLK)
/LED_HALO_A_N: J10.8, L20.2
/LED_HALO_A_P: J10.7, R40.2, U21.4 (CSN)
/LED_HALO_A_SW: D20.2 (A), L20.1, U21.1 (SW)
/LED_HALO_B_N: J10.6, L19.2
/LED_HALO_B_P: J10.5, R39.2, U20.4 (CSN)
/LED_HALO_B_SW: D19.2 (A), L19.1, U20.1 (SW)
/LED_HALO_G_N: J10.4, L18.2
/LED_HALO_G_P: J10.3, R38.2, U19.4 (CSN)
/LED_HALO_G_SW: D18.2 (A), L18.1, U19.1 (SW)
/LED_HALO_R_N: J10.2, L17.2
/LED_HALO_R_P: J10.1, R37.2, U18.4 (CSN)
/LED_HALO_R_SW: D17.2 (A), L17.1, U18.1 (SW)
/LED_L1_AMB_N: J7.6, L13.2
/LED_L1_AMB_P: J7.5, R33.2, U14.4 (CSN)
/LED_L1_AMB_SW: D13.2 (A), L13.1, U14.1 (SW)
/LED_L1_CW_N: J7.4, L12.2
/LED_L1_CW_P: J7.3, R32.2, U13.4 (CSN)
/LED_L1_CW_SW: D12.2 (A), L12.1, U13.1 (SW)
/LED_L1_WW_N: J7.2, L11.2
/LED_L1_WW_P: J7.1, R31.2, U12.4 (CSN)
/LED_L1_WW_SW: D11.2 (A), L11.1, U12.1 (SW)
/LED_L2_AMB_N: J8.6, L16.2
/LED_L2_AMB_P: J8.5, R36.2, U17.4 (CSN)
/LED_L2_AMB_SW: D16.2 (A), L16.1, U17.1 (SW)
/LED_L2_CW_N: J8.4, L15.2
/LED_L2_CW_P: J8.3, R35.2, U16.4 (CSN)
/LED_L2_CW_SW: D15.2 (A), L15.1, U16.1 (SW)
/LED_L2_WW_N: J8.2, L14.2
/LED_L2_WW_P: J8.1, R34.2, U15.4 (CSN)
/LED_L2_WW_SW: D14.2 (A), L14.1, U15.1 (SW)
/LORA_ANT: J6.1 (In), U7.1 (ANT)
/LORA_CS: R27.2, U1.18 (IO10), U7.15 (~NSS)
/LORA_DIO0: U1.32 (IO39), U7.5 (DIO0)
/LORA_RST: U1.22 (IO14), U7.4 (~RESET)
/MAINS_OK: R8.2, U1.4 (IO4), U3.17 (PG)
/MCU_BOOT: R12.2, SW2.1, U1.27 (IO0)
/MCU_EN: C7.1, R24.2, SW1.1, U1.3 (EN)
/NAND_CS: R28.2, U1.17 (IO9), U8.1 (CS_N)
/PVDD_24V: C9.1, C10.1, D1.1 (K), D2.1 (K), D3.1 (K), R16.1, U4.2 (VIN), U4.3 (EN), U6.17 (PVDD_A1), U6.18 (PVDD_A2), U6.25 (PVDD_B1), U6.26 (PVDD_B2)
/PWM_CH1: U2.26 (IO4), U12.3 (DIM)
/PWM_CH2: U2.16 (IO13), U13.3 (DIM)
/PWM_CH3: U2.13 (IO14), U14.3 (DIM)
/PWM_CH4: U2.30 (IO18), U15.3 (DIM)
/PWM_CH5: U2.31 (IO19), U16.3 (DIM)
/PWM_CH6: U2.33 (IO21), U17.3 (DIM)
/PWM_CH7: U2.37 (IO23), U18.3 (DIM)
/PWM_CH8: U2.12 (IO27), U19.3 (DIM)
/PWM_CH9: U2.8 (IO32), U20.3 (DIM)
/PWM_CH10: U2.9 (IO33), U21.3 (DIM)
/RTC_INT_N: R14.2, U1.34 (IO41), U9.3 (INT_N)
/SPI_MISO: U1.21 (IO13), U7.13 (MISO), U8.2 (DO_IO1)
/SPI_MOSI: U1.19 (IO11), U7.14 (MOSI), U8.5 (DI_IO0)
/SPI_SCK: U1.20 (IO12), U7.12 (SCK), U8.6 (CLK)
/SPK_LN: C12.1, J5.2, L3.2
/SPK_LP: C11.1, J5.1, L2.2
/SPK_RN: C13.1, J5.4, L4.2
/SPK_RP: C14.1, J5.3, L5.2
/STATUS_LED_3V3: R9.1, U1.35 (IO42)
/STATUS_LED_DIN: D4.2 (DIN), R9.2
/UART0_RX: J4.2, U1.36 (RXD0)
/UART0_TX: J4.1, U1.37 (TXD0)
/USB_CC1: J3.A5 (CC1), R22.1
/USB_CC2: J3.B5 (CC2), R23.1
/USB_DN: U1.13 (USB_D-), U11.6 (IO1_OUT)
/USB_DN_CON: J3.A7 (DN1), J3.B7 (DN2), U11.1 (IO1_IN)
/USB_DP: U1.14 (USB_D+), U11.4 (IO2_OUT)
/USB_DP_CON: J3.A6 (DP1), J3.B6 (DP2), U11.3 (IO2_IN)
/VBAT_RTC: BT1.1 (+), U9.6 (VBAT)

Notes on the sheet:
1. 24V MAINS + 4S LiFePO4 UPS (BQ24610) + 24V ALARM BOOST (TPS55340) + 5V/3.3V BUCKS
2. MAIN MCU: ESP32-S3-WROOM-1-N16R8 + NATIVE USB-C (USBLC6 ESD) + STATUS LED
3. BLUETOOTH A2DP + 10-CH PWM LED CO-PROCESSOR (ESP32-WROOM-32E)
4. STEREO 2x40W CLASS-D I2S AMPLIFIER (TAS5825M HTSSOP-32 + BOOTSTRAP + LC)
5. LORA 868 MHz (Ai-Thinker Ra-01H) + 1Gbit SPI NAND (W25N01GV) + RTC (DS3231MZ)
6. 10-CH CONSTANT-CURRENT DAWN & HALO LED DRIVERS (10x PT4115 ON MAINS-ONLY 24V)

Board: 4 copper layers, 149 parts (0 on the bottom side), 121 nets, no tracks yet.

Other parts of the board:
MH1, MH2, MH3, MH4: MountingHole_3.2mm; MountingHole_3.2mm_M3
